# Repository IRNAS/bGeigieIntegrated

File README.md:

# bGeigieIntegrated
#### Integrated version of Safecast bGeigie device

We created an integrated version of the bGeigie device, a mobile survey Geiger counter. Our PCB is based on orginal design by [Safecast](https://github.com/Safecast/bGeigieNanoKit). We removed various breakout boards and instead placed most of the components directly on the PCB. Our design uses [RedBear Duo](https://github.com/redbear/Duo) as a central processing unit, instead of Arduino Fio. The entire circuit can be powered through USB connector on RedBear, or from a 3.7V LiPo battery. The circuit also includes a battery charger. For control of the Geiger gas tube the iRover is being used, just like in the original design. A LED and a piezo buzzer signalyze the incoming pulses. FGPMMOPA6H GPS receiver from Adafruit retrieves the current position of the device and an accelerometer/magnetometer (LSM303C form ST Microelectronics) measures acceleration and orientation of it. Data are being logged on a micro SD card. A socket for the XBee module is also included, which enables connection to an external logger. A monochrome, 128x32 pixels wide OLED graphical display from [Adafruit](https://www.adafruit.com/product/938) displays a simple user interface. Accelerometer/magnetometer uses an I2C interface. SD card and OLED display communicate via SPI. XBee and GPS module are using an UART interface.

-

#### Changes in schematic:

* Power supply:
 * automatic switch between battery or USB powered mode
 * software power-down
* GPS module:
 * connection to battery
 * uFL connector for external antenna
* OLED display:
 * changed to I2C interface
 * added socket for alternative [display](https://www.amazon.com/Diymall%C2%AE-Yellow-Serial-Arduino-Display/dp/B00O2LLT30)
* magnetic buzzer with integrated oscillator
* high brigthess LEDs for COUNT and LOG indication
* added rotary encoder

---

#### License

All our projects are as usefully open-source as possible.

Hardware including documentation is licensed under [CERN OHL v.1.2. license](http://www.ohwr.org/licenses/cern-ohl/v1.2)

Firmware and software originating from the project is licensed under [GNU GENERAL PUBLIC LICENSE v3](http://www.gnu.org/licenses/gpl-3.0.en.html).

Open data generated by our projects is licensed under [CC0](https://creativecommons.org/publicdomain/zero/1.0/legalcode).

All our websites and additional documentation are licensed under [Creative Commons Attribution-ShareAlike 4 .0 Unported License] (https://creativecommons.org/licenses/by-sa/4.0/legalcode).

What this means is that you can use hardware, firmware, software and documentation without paying a royalty and knowing that you'll be able to use your version forever. You are also free to make changes but if you share these changes then you have to do so on the same conditions that you enjoy.

Koruza, GoodEnoughCNC and IRNAS are all names and marks of Institut IRNAS Rače. 
You may use these names and terms only to attribute the appropriate entity as required by the Open Licences referred to above. You may not use them in any other way and in particular you may not use them to imply endorsement or authorization of any hardware that you design, make or sell.

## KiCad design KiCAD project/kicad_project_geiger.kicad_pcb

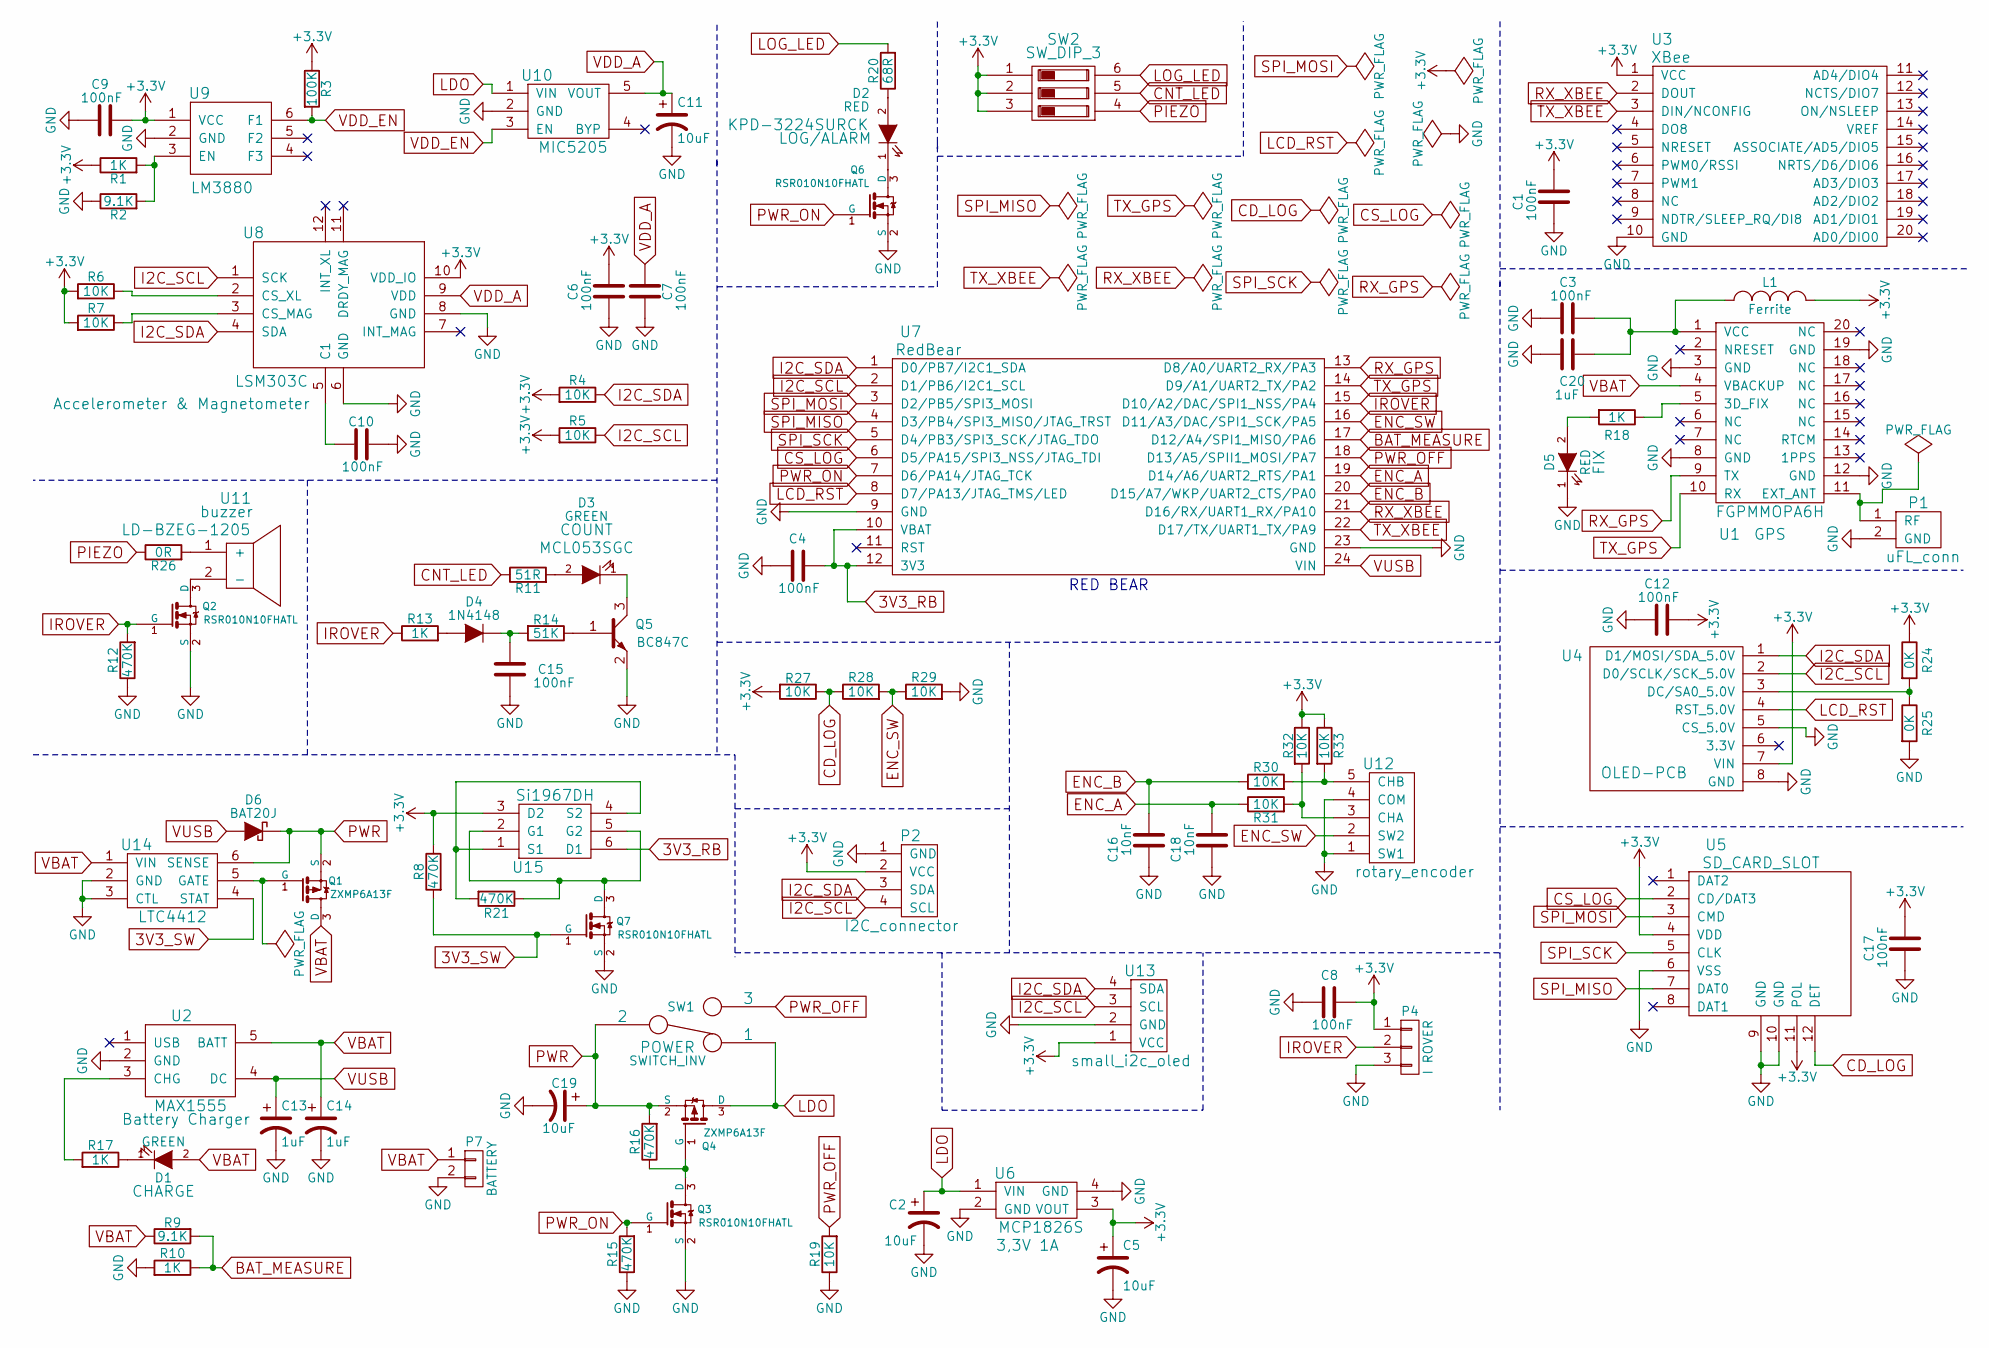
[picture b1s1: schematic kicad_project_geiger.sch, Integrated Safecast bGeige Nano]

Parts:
C1, C3, C4, C6, C7, C8, C9, C10, C12, C15, C17: 100nF; R_0603_HandSoldering
C2, C5, C11, C19: 10uF; TantalC_SizeB_EIA-3528_HandSoldering
C13, C14: 1uF; TantalC_SizeB_EIA-3528_HandSoldering
C16, C18: 10nF; R_0603_HandSoldering
C20: 1uF; R_0603_HandSoldering
D1: GREEN; LED_0603_HandSoldering
D2: RED; KPD-3224SURCK
D3: GREEN; MCL053SGC
D4: 1N4148; SOD-323
D5: RED; LED_0603_HandSoldering
D6: BAT20J; SOD-323
L1: Ferrite; R_0603_HandSoldering
P1: uFL_conn; U.FL-R-SMT
P2: I2C_connector; DIP_Grove_4P-2_0
P4: I ROVER; B3B-PH-SM4-TB_IROVER_CONNECTOR
P7: BATTERY; B2B-PH-SM4-TB_Battery_Connector
Q1, Q4: ZXMP6A13F; SOT-23
Q2, Q3, Q6, Q7: RSR010N10FHATL; SOT-23
Q5: BC847C; SOT-23
R1, R10, R13, R17, R18: 1K; R_0603_HandSoldering
R2, R9: 9.1K; R_0603_HandSoldering
R3: 100K; R_0603_HandSoldering
R4, R5, R6, R7, R19, R27, R28, R29, R30, R31, R32, R33: 10K; R_0603_HandSoldering
R8, R12, R15, R16, R21: 470K; R_0603_HandSoldering
R11: 51R; R_0603_HandSoldering
R14: 51K; R_0603_HandSoldering
R20: 68R; R_0603_HandSoldering
R24, R25: 0K; R_0603_HandSoldering
R26: 0R; R_0603_HandSoldering
SW1: SWITCH_INV; OS102011MA1QN1_slide_switch
SW2: SW_DIP_3; OMRON_ELECTRONIC_COMPONENTS_A6S-3102-H_DIP_Switch
U1: FGPMMOPA6H; FGPMMOPA6H_GPS
U2: MAX1555; SOT-23-5
U3: XBee; xbee
U4: OLED-PCB; Adafruit-1_3inch-128x64-Mono-OLED-PCB-master
U5: SD_CARD_SLOT; MOLEX_47309-2651_CONNECTOR_MICRO_SD
U6: MCP1826S; MCP1826S_SOT223
U7: RedBear
U8: LSM303C
U9: LM3880
U10: MIC5205
U11: buzzer; LD-BZEG-1205
U12: rotary_encoder; rotary_enc_bourns_EC12R-4215F-S0024
U13: small_i2c_oled; Small_I2C_OLED
U14: LTC4412
U15: Si1967DH

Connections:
3V3_RB: C4.2, U7.10 (VBAT), U7.12 (3V3), U15.6 (D1)
3V3_SW: Q7.1 (G), R8.2, U14.4 (STAT)
+3V3: C1.2, C5.1, C6.2, C8.1, C9.2, C12.2, C17.2, L1.2, P2.2 (VCC), P4.1, R1.1, R3.1, R4.2, R5.2, R6.2, R7.2, R8.1, R24.1, R27.2, R32.1, R33.1, SW2.1, SW2.2, SW2.3, U3.1 (VCC), U4.7 (VIN), U5.4 (VDD), U5.11 (POL), U6.3 (VOUT), U8.10 (VDD_IO), U9.1 (VCC), U13.1 (VCC), U15.3 (D2)
BAT_MEASURE: R9.2, R10.1, U7.17 (D12/A4/SPI1_MISO/PA6)
CD_LOG: R27.1, R28.1, U5.12 (DET)
CNT_LED: R11.1, SW2.5
CS_LOG: U5.2 (CD/DAT3), U7.6 (D5/PA15/SPI3_NSS/JTAG_TDI)
ENC_A: C18.2, R31.1, U7.19 (D14/A6/UART2_RTS/PA1)
ENC_B: C16.2, R30.1, U7.20 (D15/A7/WKP/UART2_CTS/PA0)
ENC_SW: R28.2, R29.1, U7.16 (D11/A3/DAC/SPI1_SCK/PA5), U12.2 (SW2)
GND: C1.1, C2.2, C3.2, C4.1, C5.2, C6.1, C7.1, C8.2, C9.1, C10.2, C11.2, C12.1, C13.2, C14.2, C15.2, C16.1, C17.1, C18.1, C19.2, C20.2, D5.1 (K), P1.2 (GND), P2.1 (GND), P4.3, P7.2, Q2.2 (S), Q3.2 (S), Q5.2 (E), Q6.2 (S), Q7.2 (S), R2.1, R10.2, R12.1, R15.1, R19.1, R25.2, R29.2, U1.3 (GND), U1.8 (GND), U1.12 (GND), U1.19 (GND), U2.2 (GND), U3.10 (GND), U4.5 (CS_5.0V), U4.8 (GND), U5.6 (VSS), U5.9 (GND), U5.10 (GND), U6.2 (GND), U6.4 (GND), U7.9 (GND), U7.23 (GND), U8.6 (GND), U8.8 (GND), U9.2 (GND), U10.2 (GND), U12.1 (SW1), U12.4 (COM), U13.2 (GND), U14.2 (GND), U14.3 (CTL)
I2C_SCL: P2.4 (SCL), R5.1, U4.2 (D0/SCLK/SCK_5.0V), U7.2 (D1/PB6/I2C1_SCL), U8.1 (SCK), U13.3 (SCL)
I2C_SDA: P2.3 (SDA), R4.1, U4.1 (D1/MOSI/SDA_5.0V), U7.1 (D0/PB7/I2C1_SDA), U8.4 (SDA), U13.4 (SDA)
IROVER: P4.2, Q2.1 (G), R12.2, R13.1, U7.15 (D10/A2/DAC/SPI1_NSS/PA4)
LCD_RST: U4.4 (RST_5.0V), U7.8 (D7/PA13/JTAG_TMS/LED)
LDO: C2.1, Q4.3 (D), SW1.1, U6.1 (VIN), U10.1 (VIN)
LOG_LED: R20.2, SW2.6
unnamed: C10.1, U8.5 (C1)
unnamed: C15.1, D4.1 (K), R14.2
unnamed: C3.1, C20.1, L1.1, U1.1 (VCC)
unnamed: D1.1 (K), R17.1
unnamed: D2.1 (K), Q6.3 (D)
unnamed: D2.2 (A), R20.1
unnamed: D3.1 (K), Q5.3 (C)
unnamed: D3.2 (A), R11.2
unnamed: D4.2 (A), R13.2
unnamed: D5.2 (A), R18.2
unnamed: P1.1 (RF), U1.11 (EXT_ANT)
unnamed: Q1.1 (G), U14.5 (GATE)
unnamed: Q2.3 (D), U11.2 (-)
unnamed: Q3.3 (D), Q4.1 (G), R16.1
unnamed: Q5.1 (B), R14.1
unnamed: Q7.3 (D), R21.1, U15.2 (G1), U15.5 (G2)
unnamed: R1.2, R2.2, U9.3 (EN)
unnamed: R6.1, U8.2 (CS_XL)
unnamed: R7.1, U8.3 (CS_MAG)
unnamed: R17.2, U2.3 (CHG)
unnamed: R18.1, U1.5 (3D_FIX)
unnamed: R21.2, U15.1 (S1), U15.4 (S2)
unnamed: R24.2, R25.1, U4.3 (DC/SA0_5.0V)
unnamed: R26.2, U11.1 (+)
unnamed: R30.2, R33.2, U12.5 (CHB)
unnamed: R31.2, R32.2, U12.3 (CHA)
PIEZO: R26.1, SW2.4
PWR: C19.1, D6.1 (K), Q1.2 (S), Q4.2 (S), R16.2, SW1.2, U14.6 (SENSE)
PWR_OFF: R19.2, SW1.3, U7.18 (D13/A5/SPII1_MOSI/PA7)
PWR_ON: Q3.1 (G), Q6.1 (G), R15.2, U7.7 (D6/PA14/JTAG_TCK)
RX_GPS: U1.9 (TX), U7.13 (D8/A0/UART2_RX/PA3)
RX_XBEE: U3.2 (DOUT), U7.21 (D16/RX/UART1_RX/PA10)
SPI_MISO: U5.7 (DAT0), U7.4 (D3/PB4/SPI3_MISO/JTAG_TRST)
SPI_MOSI: U5.3 (CMD), U7.3 (D2/PB5/SPI3_MOSI)
SPI_SCK: U5.5 (CLK~), U7.5 (D4/PB3/SPI3_SCK/JTAG_TDO)
TX_GPS: U1.10 (RX), U7.14 (D9/A1/UART2_TX/PA2)
TX_XBEE: U3.3 (DIN/NCONFIG), U7.22 (D17/TX/UART1_TX/PA9)
VBAT: C14.1, D1.2 (A), P7.1, Q1.3 (D), R9.1, U1.4 (VBACKUP), U2.5 (BATT), U14.1 (VIN)
VDD_A: C7.2, C11.1, U8.9 (VDD), U10.5 (VOUT)
VDD_EN: R3.2, U9.6 (F1), U10.3 (EN)
VUSB: C13.1, D6.2 (A), U2.4 (DC), U7.24 (VIN)

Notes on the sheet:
RED BEAR

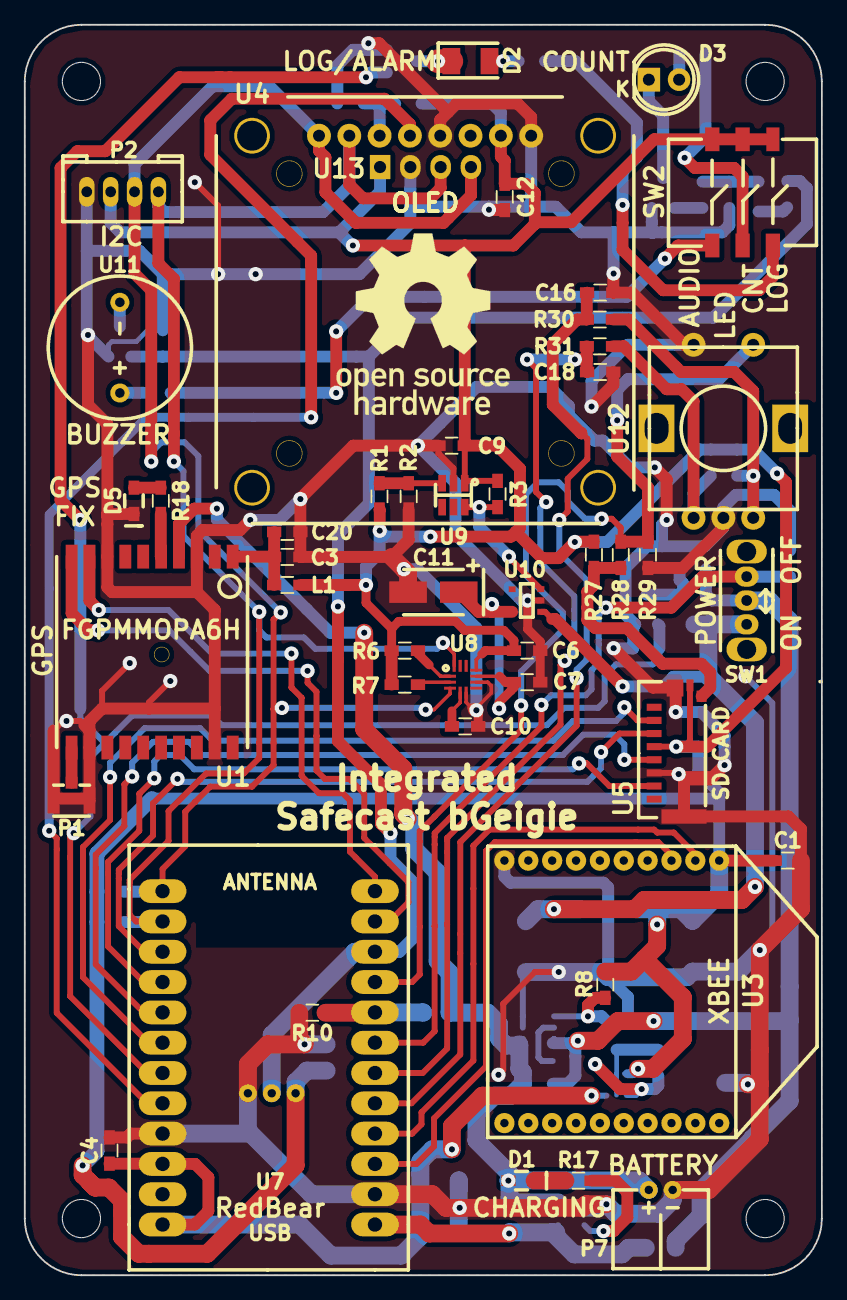
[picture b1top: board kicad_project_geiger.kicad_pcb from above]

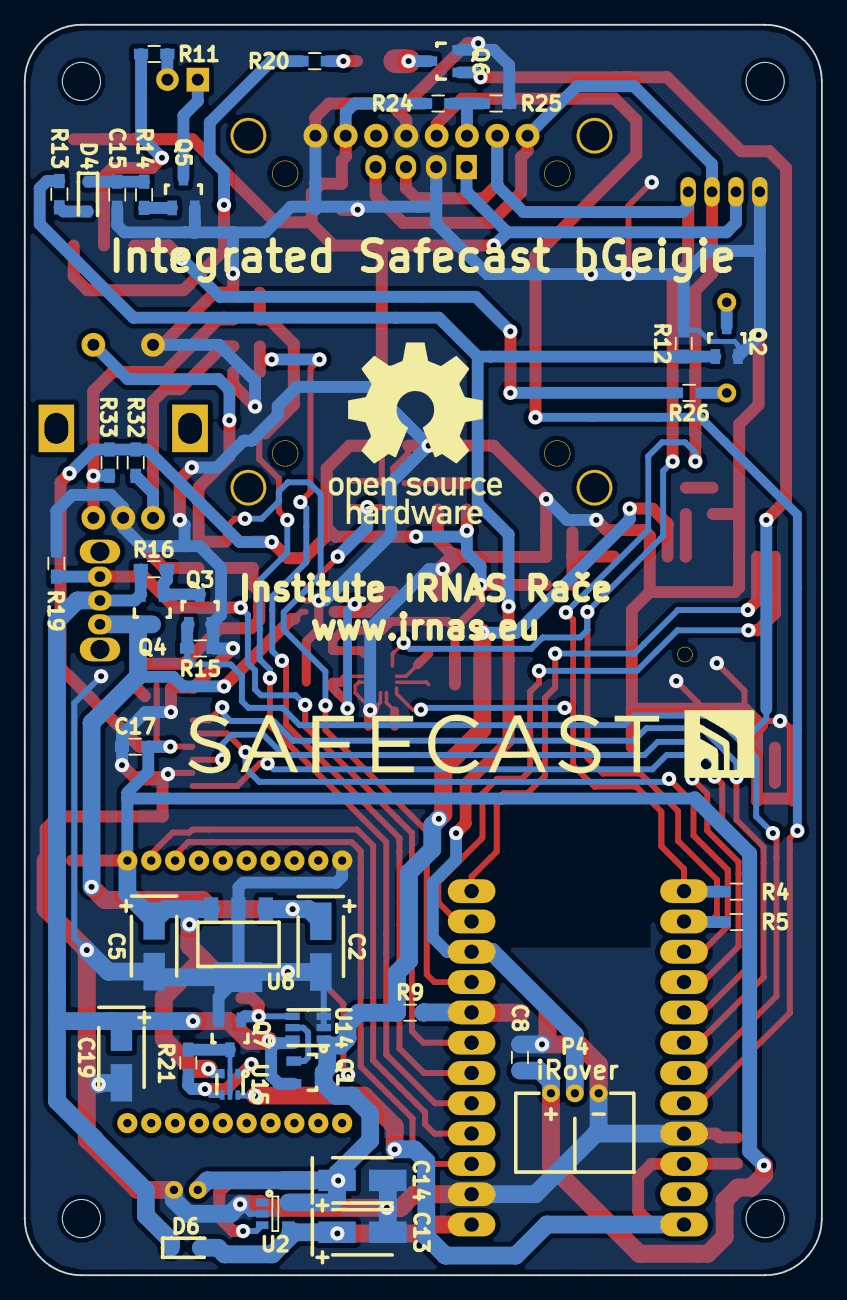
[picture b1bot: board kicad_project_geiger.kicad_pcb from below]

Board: 2 copper layers, 66.8 x 104.8 mm, 86 parts (39 on the bottom side), 58 nets.

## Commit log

2016-04-07 New schematic proposal
2016-07-11 Update
    Updated BOM and schematic.
2016-11-07 Added self test program
2016-12-26 Update in self test code
